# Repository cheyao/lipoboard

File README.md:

# LiPoboard

A 3-in-one LiPo breakout board:
- LiPo charging
- Overdischarge protection
- Conversion to 3v3 or 5v

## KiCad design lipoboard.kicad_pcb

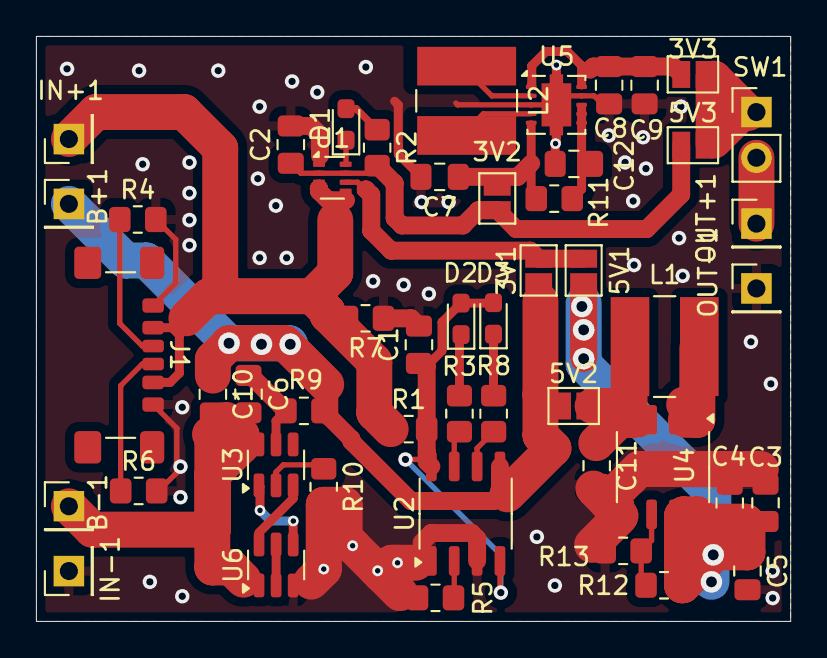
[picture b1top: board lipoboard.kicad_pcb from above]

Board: 2 copper layers, 41.9 x 32.5 mm, 50 parts (0 on the bottom side), 32 nets.

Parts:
3V1, 3V2, 3V3, 5V1, 5V2, 5V3: Jumper_2_Open; SolderJumper-2_P1.3mm_Open_Pad1.0x1.5mm
B+1: Conn_01x01_Pin; PinHeader_1x01_P2.54mm_Vertical
B-1: Conn_01x01_Pin; PinHeader_1x01_P2.54mm_Vertical
C1, C2, C3, C4, C5, C7, C8, C9, C10: 10uF; C_0805_2012Metric_Pad1.18x1.45mm_HandSolder
C6, C12: 0.1uF; C_0805_2012Metric_Pad1.18x1.45mm_HandSolder
C11: 22uF; C_0805_2012Metric_Pad1.18x1.45mm_HandSolder
D1, D3: GLED; LED_0603_1608Metric_Pad1.05x0.95mm_HandSolder
D2: RLED; LED_0603_1608Metric_Pad1.05x0.95mm_HandSolder
IN+1: Conn_01x01_Pin; PinHeader_1x01_P2.54mm_Vertical
IN-1: Conn_01x01_Pin; PinHeader_1x01_P2.54mm_Vertical
J1: USB_C_Receptacle_PowerOnly_24P; USB_C_Receptacle_GCT_USB4135-GF-A_6P_TopMnt_Horizontal
L1, L2: 2.2uH; L_TracoPower_TCK-047_5.2x5.8mm
OUT+1: Conn_01x01_Pin; PinHeader_1x01_P2.54mm_Vertical
OUT-1: Conn_01x01_Pin; PinHeader_1x01_P2.54mm_Vertical
R1: 0.4Ω; R_0805_2012Metric_Pad1.20x1.40mm_HandSolder
R2, R3, R8: 1kΩ; R_0805_2012Metric_Pad1.20x1.40mm_HandSolder
R4, R6: 5.1kΩ; R_0805_2012Metric_Pad1.20x1.40mm_HandSolder
R5: 1.33kΩ; R_0805_2012Metric_Pad1.20x1.40mm_HandSolder
R7: 10kΩ; R_0805_2012Metric_Pad1.20x1.40mm_HandSolder
R9: 470Ω; R_0805_2012Metric_Pad1.20x1.40mm_HandSolder
R10: 2kΩ; R_0805_2012Metric_Pad1.20x1.40mm_HandSolder
R11: 100Ω; R_0805_2012Metric_Pad1.20x1.40mm_HandSolder
R12: 300kΩ; R_0805_2012Metric_Pad1.20x1.40mm_HandSolder
R13: 75kΩ; R_0805_2012Metric_Pad1.20x1.40mm_HandSolder
SW1: SW_DIP_x01; PinHeader_1x02_P2.54mm_Vertical
U1: TPS2116DRL; SOT-583-8
U2: TP4056; SOP-8_3.9x4.9mm_P1.27mm
U3: DW01A; SOT-23-6
U4: TP5188; SOP-8_3.9x4.9mm_P1.27mm
U5: TPS63001; Texas_DRC0010J
U6: 8025A; SOT-23-6

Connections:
3.3VOUT: 3V3.1 (A), C8.1, C9.1, U5.1 (VOUT), U5.10 (FB)
5VOUT: 5V1.1 (A), C3.1, C4.1, C5.1, R12.1, U4.7 (VOUT), U4.8 (VOUT)
GND: C1.2, C2.2, C3.2, C4.2, C5.2, C7.2, C8.2, C9.2, C11.2, C12.2, IN-1.1, J1.A12 (GND), J1.B12 (GND), OUT-1.1, R4.2, R5.2, R6.2, R7.1, R10.2, R13.1, U1.1 (GND), U2.1 (TEMP), U2.3 (GND), U4.5 (GND), U5.3 (PGND), U5.9 (GND), U5.11 (PGND), U6.3 (S2)
MUXOUT: 3V2.2 (B), 5V3.1 (A), C2.1, R2.2, U1.2 (VOUT), U1.7 (VOUT)
unnamed: 3V1.2 (B), 5V1.2 (B), U1.6 (VIN2)
unnamed: 3V2.1 (A), C7.1, R11.2, U5.5 (VIN)
unnamed: 3V3.2 (B), 5V3.2 (B), SW1.1
unnamed: 5V2.2 (B), C11.1, L1.1, U4.3 (BAT), U4.4 (EN)
unnamed: B-1.1, C6.2, C10.2, U3.6 (GND), U6.1 (S1)
unnamed: D1.2 (A), R2.1
unnamed: D1.1 (K), U1.8 (ST)
unnamed: D2.1 (K), R3.1
unnamed: D3.1 (K), R8.1
unnamed: J1.A5 (CC1), R4.1
unnamed: J1.B5 (CC2), R6.1
unnamed: L1.2, U4.1 (SW), U4.2 (SW)
unnamed: OUT+1.1, SW1.2
unnamed: R5.1, U2.2 (PROG)
unnamed: R3.2, U2.7 (~CHRG)
unnamed: R8.2, U2.6 (~STDBY)
unnamed: R10.1, U3.2 (CS)
unnamed: U3.3 (OC), U6.6 (G2)
unnamed: U3.1 (OD), U6.4 (G1)
unnamed: C6.1, R9.2, U3.5 (VCC)
unnamed: R12.2, R13.2, U4.6 (FB)
unnamed: C12.1, R11.1, U5.6 (EN), U5.7 (PS/SYNC), U5.8 (VINA)
unnamed: L2.2, U5.4 (L1)
unnamed: L2.1, U5.2 (L2)
unnamed: U6.2 (D1), U6.5 (D2)
VBAT: 3V1.1 (A), 5V2.1 (A), B+1.1, C10.1, R9.1, U2.5 (BAT)
VBUS: IN+1.1, J1.A9 (VBUS), J1.B9 (VBUS), R1.1, R7.2, U1.3 (VIN1), U1.4 (PR1), U1.5 (MODE)
VCRG: C1.1, D2.2 (A), D3.2 (A), R1.2, U2.4 (VCC), U2.8 (CE)

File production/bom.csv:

Designator,Footprint,Quantity,Value,LCSC Part #
"3V1, 3V2, 3V3, 5V1, 5V2, 5V3",SolderJumper-2_P1.3mm_Open_Pad1.0x1.5mm,6,Jumper_2_Open,
"B+, B-, IN+, IN-, OUT+, OUT-",PinHeader_1x01_P2.54mm_Vertical,6,Conn_01x01_Pin,
"C1, C10, C2, C3, C4, C5, C7, C8, C9",0805,9,10uF,
C11,0805,1,22uF,
"C12, C6",0805,2,0.1uF,
"D1, D3",0603,2,GLED,
D2,0603,1,RLED,
J1,USB_C_Receptacle_GCT_USB4135-GF-A_6P_TopMnt_Horizontal,1,USB_C_Receptacle_PowerOnly_24P,
"L1, L2",L_TracoPower_TCK-047_5.2x5.8mm,2,2.2uH,
R1,0805,1,0.4Ω,
R10,0805,1,2kΩ,
R11,0805,1,100,
R12,0805,1,300kΩ,
R13,0805,1,75kΩ,
"R2, R3, R8",0805,3,1kΩ,
"R4, R6",0805,2,5.1kΩ,
R5,0805,1,1.33kΩ,
R7,0805,1,10kΩ,
R9,0805,1,470Ω,
SW1,PinHeader_1x02_P2.54mm_Vertical,1,SW_DIP_x01,
U1,SOT-583-8,1,TPS2116DRL,
"U2, U4",SOP-8_3.9x4.9mm_P1.27mm,2,~,
U3,SOT-23-6,1,DW01A,
U5,Texas_DRC0010J_ThermalVias,1,TPS63001,
U6,SOT-23-6,1,~,

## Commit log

2025-02-27 init
2025-02-28 Init!
2025-03-08 Add readme
2025-03-08 Change dir structure
